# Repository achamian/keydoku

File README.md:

# Keydoku

## Rules

* Fill in the digits 1 to 9 in the grid.
* Set of three sequential cells along the orange line must contain a low digit (123), a middle digit (456) and a high digit (789).
* Digits on the orange line have same modulo 3.
* Digit in the circle is sum of the digits on the attached line.
* Digit outside the grid is either a Sky Scrapper clue or represnt sum of the digits on corrosponding row, column or diagonal.

# Keymap

### Things To Note

* Holding down the `Corner`, `Center` or `Colour` keys will switch to respective mode till the key is released.u
* Holding down `Digit` key will enable arrow keys, escape and delete.

### Update default keymap

Default keymap can be changed by visiting [Vial](https://vial.rocks/) while keyboard is connected.

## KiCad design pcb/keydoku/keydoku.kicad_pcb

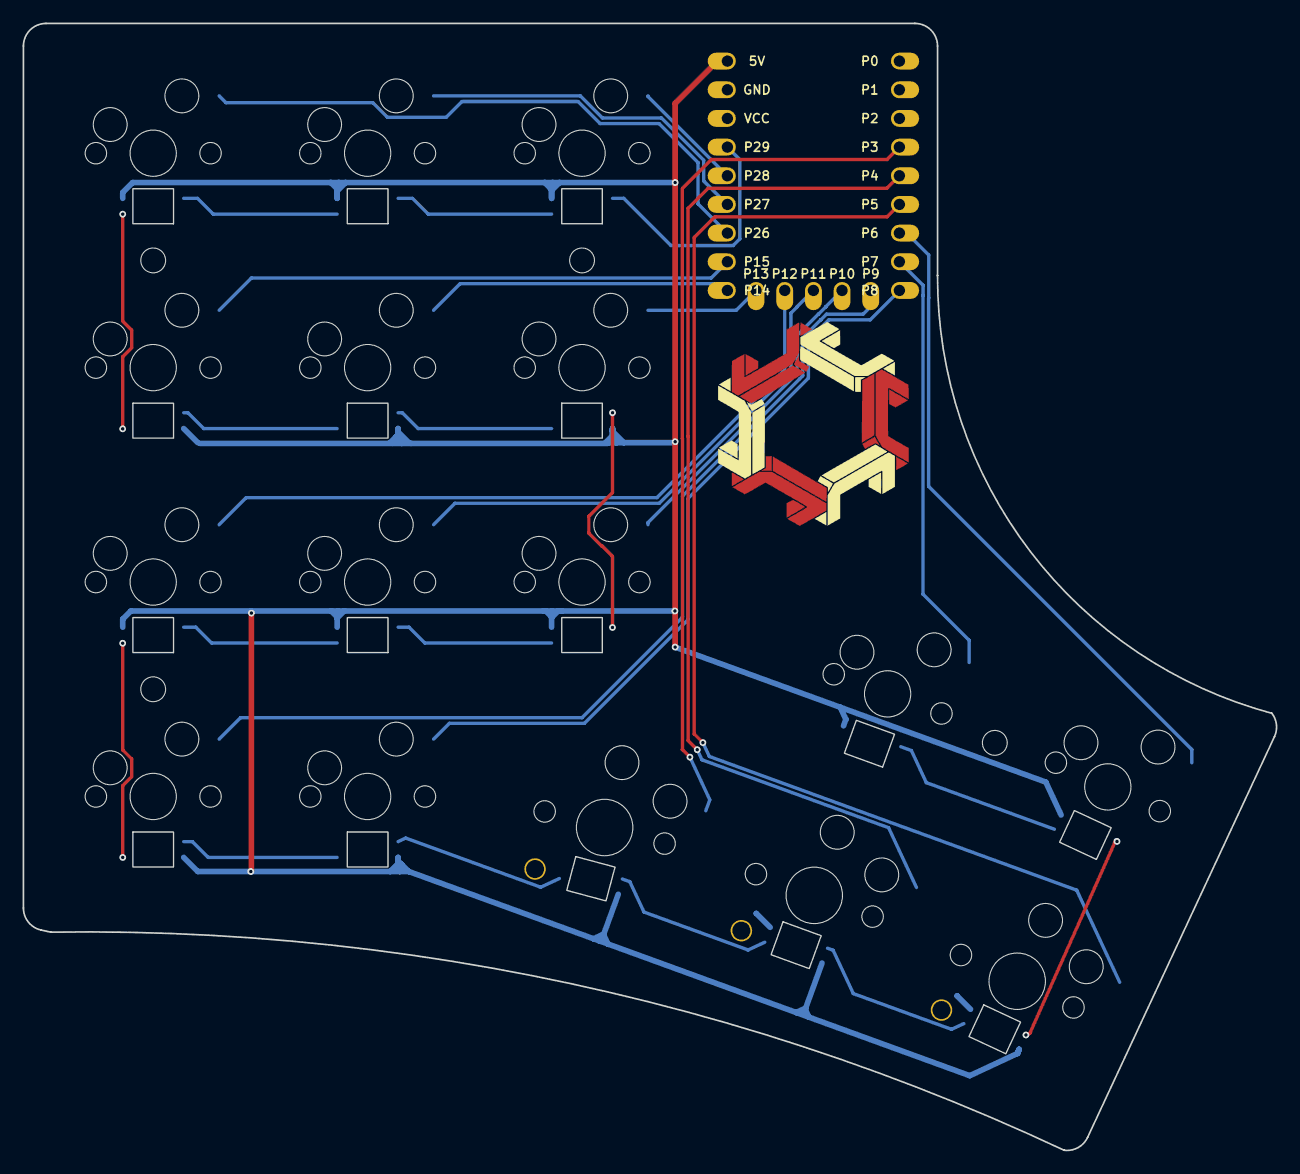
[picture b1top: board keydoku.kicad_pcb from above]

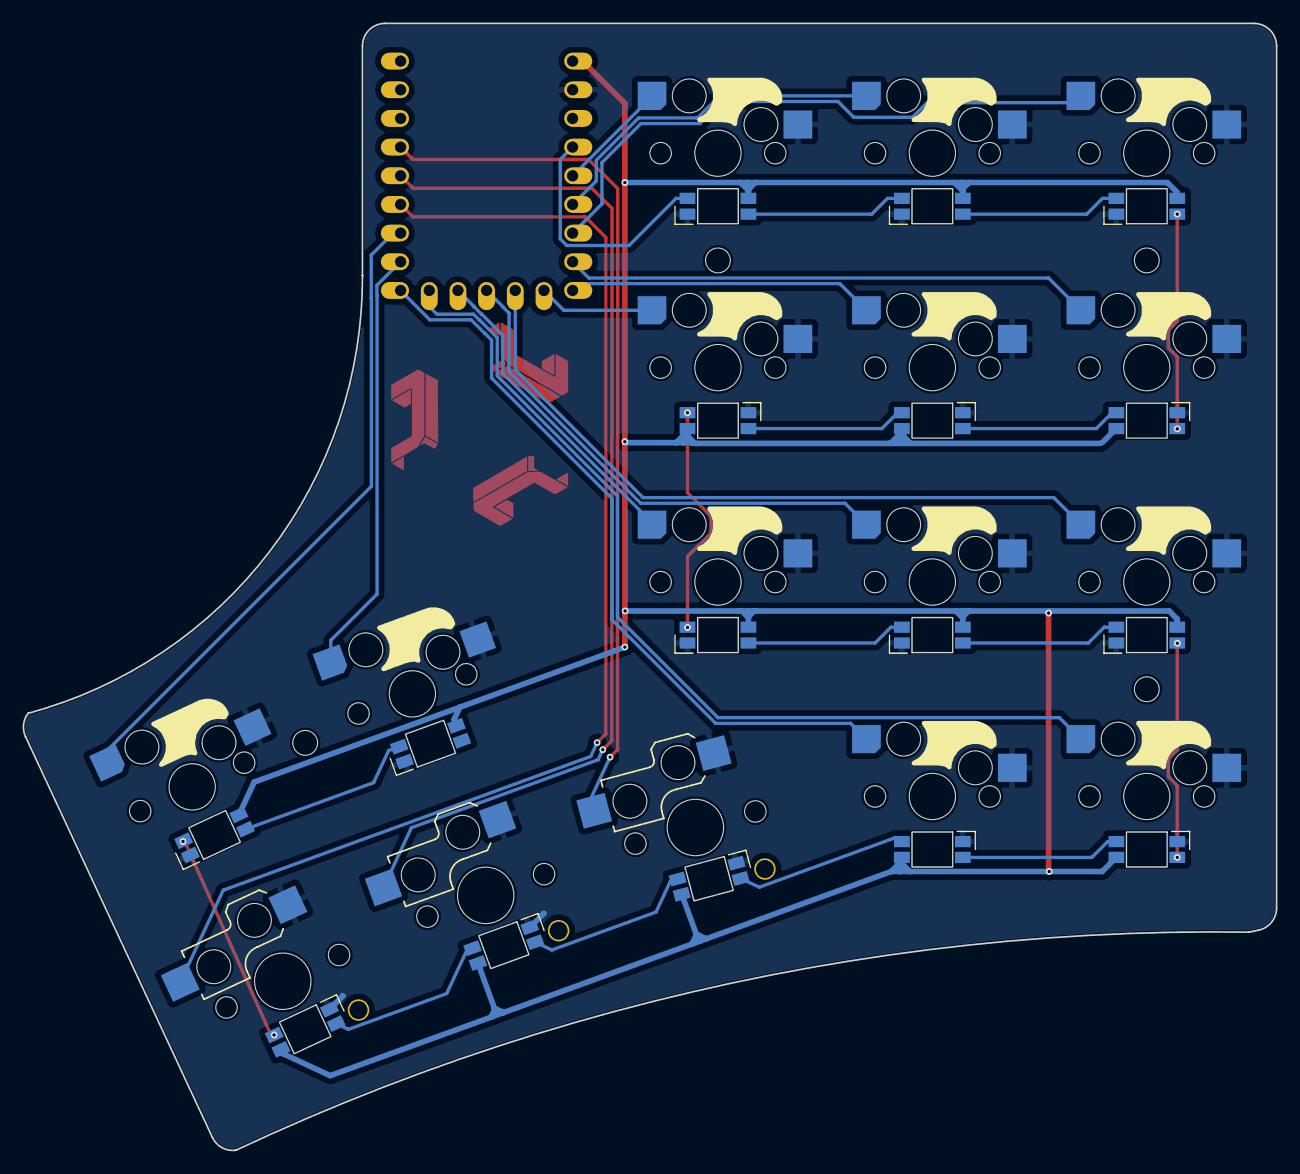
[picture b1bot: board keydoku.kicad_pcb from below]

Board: 2 copper layers, 111.0 x 99.9 mm, 37 parts (32 on the bottom side), 34 nets.

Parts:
LED1, LED2, LED3, LED4, LED5, LED6, LED7, LED8, LED9, LED10, LED11, LED12, LED13, LED14, LED15, LED16: led_SK6812mini-e (per-keysingle-side)
MCU1: Waveshare RP2040 Zero
MH1, MH2, MH3, MH4: mounting_hole_npth
S1, S2, S3, S4, S5, S6, S7, S8, S9, S10, S11, S12, S13: switch_mx
S14, S15, S16: switch_choc_v1_v2

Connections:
GND: LED1.3, LED2.3, LED3.3, LED4.3, LED5.3, LED6.3, LED7.3, LED8.3, LED9.3, LED10.3, LED11.3, LED12.3, LED13.3, LED14.3, LED15.3, LED16.3, MCU1.22, S1.1, S2.1, S3.1, S4.1, S5.1, S6.1, S7.1, S8.1, S9.1, S10.1, S11.1, S12.1, S13.1, S14.1, S15.1, S16.1
LED_1: LED6.4, MCU1.20
LED_2: LED4.4, LED6.2
LED_3: LED2.4, LED4.2
LED_4: LED2.2, LED10.4
LED_5: LED10.2, LED12.4
LED_6: LED12.2, LED13.4
LED_7: LED5.4, LED13.2
LED_8: LED3.4, LED5.2
LED_9: LED1.4, LED3.2
LED_10: LED1.2, LED9.4
LED_11: LED9.2, LED11.4
LED_12: LED11.2, LED14.4
LED_13: LED14.2, LED15.4
LED_14: LED15.2, LED16.4
LED_15: LED8.4, LED16.2
LED_16: LED7.4, LED8.2
P3: MCU1.4, S14.2
P4: MCU1.5, S15.2
P5: MCU1.6, S16.2
P6: MCU1.7, S13.2
P7: MCU1.8, S12.2
P8: MCU1.9, S5.2
P9: MCU1.10, S1.2
P10: MCU1.11, S9.2
P11: MCU1.12, S6.2
P12: MCU1.13, S2.2
P13: MCU1.14, S10.2
P14: MCU1.15, S7.2
P15: MCU1.16, S3.2
P26: MCU1.17, S4.2
P27: MCU1.18, S8.2
P28: MCU1.19, S11.2
VCC5V: LED1.1, LED2.1, LED3.1, LED4.1, LED5.1, LED6.1, LED7.1, LED8.1, LED9.1, LED10.1, LED11.1, LED12.1, LED13.1, LED14.1, LED15.1, LED16.1, MCU1.23

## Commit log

2024-10-28 In the beginning there was darkness
2024-10-28 Let there be light!
2024-10-29 Basic plate design with mx switches and rp2040
2024-10-29 Adding per key LEDs
2024-10-29 Adding key nets and mounting holes
2024-11-01 Moving MCU silkscreen inside and adding choc outline
2024-11-01 Removing User.Drawings from PCB
2024-11-01 Adding CTC logo as a footprint
2024-11-01 Rotate per key leds and add CTC footprint
2024-11-01 VCC traces in place
2024-11-01 All traces except GND
2024-11-01 Rounded traces
2024-11-01 PCB complete
2024-11-02 Adding various outlines required to build a case
2024-11-04 Bottom case done
2024-11-04 Top and bottom case design
2024-11-06 Adding JLCPCB gerber
2024-11-06 Adding a Makefile and package.json
2024-11-07 Adding keydoku qmk firmware
2024-11-08 Adding keydoku puzzle image
2024-11-08 Fixing keydoku puzzle image
2024-11-08 Add puzzle to the README
2024-11-08 Create default firmware and keymap
2024-11-08 Adding support for Vial
2024-11-08 Fixing README
